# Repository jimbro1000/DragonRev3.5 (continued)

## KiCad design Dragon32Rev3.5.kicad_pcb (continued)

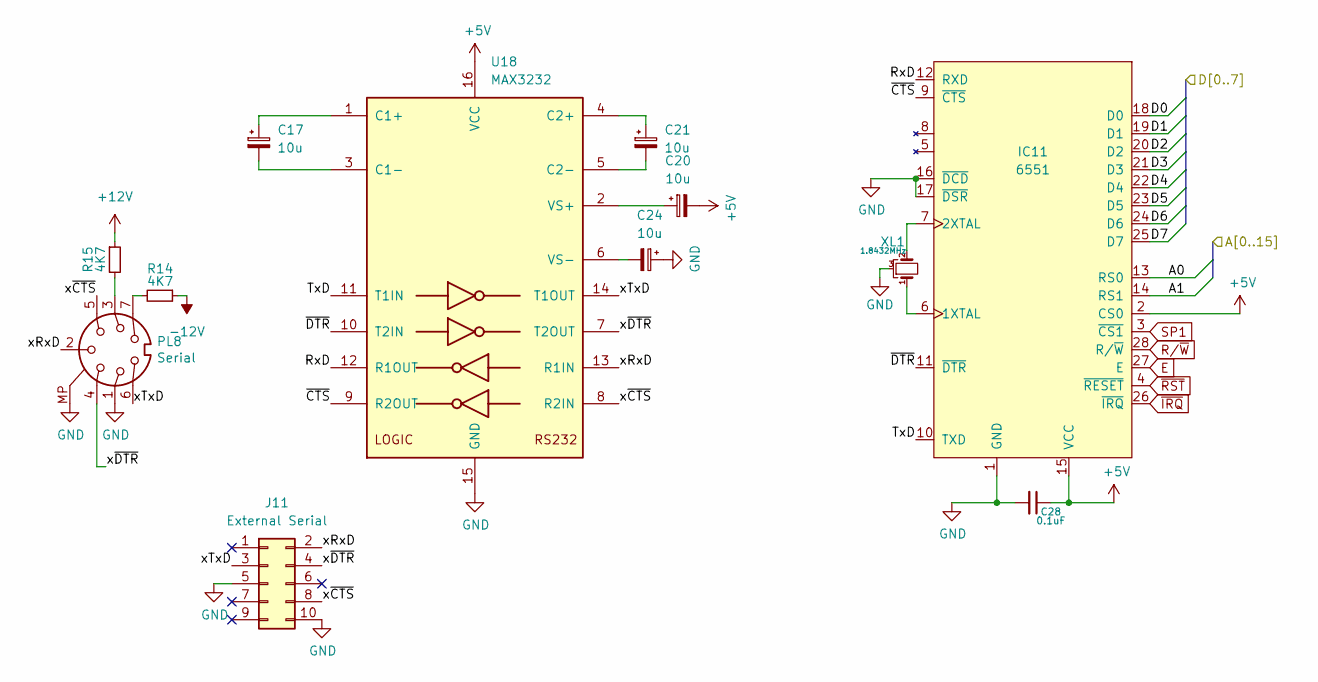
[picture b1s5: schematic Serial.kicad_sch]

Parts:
C17, C20, C21, C24: 10u; CP_EIA-3528-21_Kemet-B; DigiKey 478-5257-1-ND
C28: 0.1uF; C_0805_2012Metric
IC11: 6551; DIP-28_W15.24mm_Socket
J11: External Serial; IDC-Header_2x05_P2.54mm_Vertical
PL8: Serial; DIN-7_DELTRON_671-0701_Horizontal
R14, R15: 4K7; R_0402_1005Metric; DigiKey YAG1446CT-ND
U18: MAX3232; SOIC-16_3.9x9.9mm_P1.27mm; DigiKey 296-19851-1-ND
XL1: 1.8432MHz; Crystal_HC49-U_Horizontal_1EP_style2; DigiKey 2151-A-1.8432-18-ND

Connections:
+5V: C20.2, C28.1, IC11.2 (CS0), IC11.15 (VCC), U18.16 (VCC); also elsewhere on the board
+12V: R15.1; also elsewhere on the board
-12V: R14.1; also elsewhere on the board
/Audio/A0: IC11.13 (RS0); also elsewhere on the board
/Audio/A1: IC11.14 (RS1); also elsewhere on the board
/Audio/D0: IC11.18 (D0); also elsewhere on the board
/Audio/D1: IC11.19 (D1); also elsewhere on the board
/Audio/D2: IC11.20 (D2); also elsewhere on the board
/Audio/D3: IC11.21 (D3); also elsewhere on the board
/Audio/D4: IC11.22 (D4); also elsewhere on the board
/Audio/D5: IC11.23 (D5); also elsewhere on the board
/Audio/D6: IC11.24 (D6); also elsewhere on the board
/Audio/D7: IC11.25 (D7); also elsewhere on the board
/Serial/RxD: IC11.12 (RXD), U18.12 (R1OUT)
/Serial/TxD: IC11.10 (TXD), U18.11 (T1IN)
/Serial/xRxD: J11.2, PL8.2, U18.13 (R1IN)
/Serial/xTxD: J11.3, PL8.6, U18.14 (T1OUT)
/Serial/x~CTS: J11.8, PL8.5, U18.8 (R2IN)
/Serial/x~DTR: J11.4, PL8.4, U18.7 (T2OUT)
/Serial/~CTS: IC11.9 (~CTS), U18.9 (R2OUT)
/Serial/~DTR: IC11.11 (~DTR), U18.10 (T2IN)
E: IC11.27 (E); also elsewhere on the board
GND: C24.1, C28.2, IC11.1 (GND), IC11.16 (~DCD), IC11.17 (~DSR), J11.5, J11.10, PL8.1, PL8.MP, U18.15 (GND), XL1.3; also elsewhere on the board
unnamed: IC11.6 (1XTAL), XL1.1
unnamed: IC11.7 (2XTAL), XL1.2
unnamed: PL8.3, R15.2
unnamed: PL8.7, R14.2
unnamed: C17.1, U18.1 (C1+)
unnamed: C17.2, U18.3 (C1-)
unnamed: C21.1, U18.4 (C2+)
unnamed: C21.2, U18.5 (C2-)
unnamed: C20.1, U18.2 (VS+)
unnamed: C24.2, U18.6 (VS-)
R/~W: IC11.28 (R/~W); also elsewhere on the board
SP1: IC11.3 (~CS1); also elsewhere on the board
~IRQ: IC11.26 (~IRQ); also elsewhere on the board
~RST: IC11.4 (~RESET); also elsewhere on the board

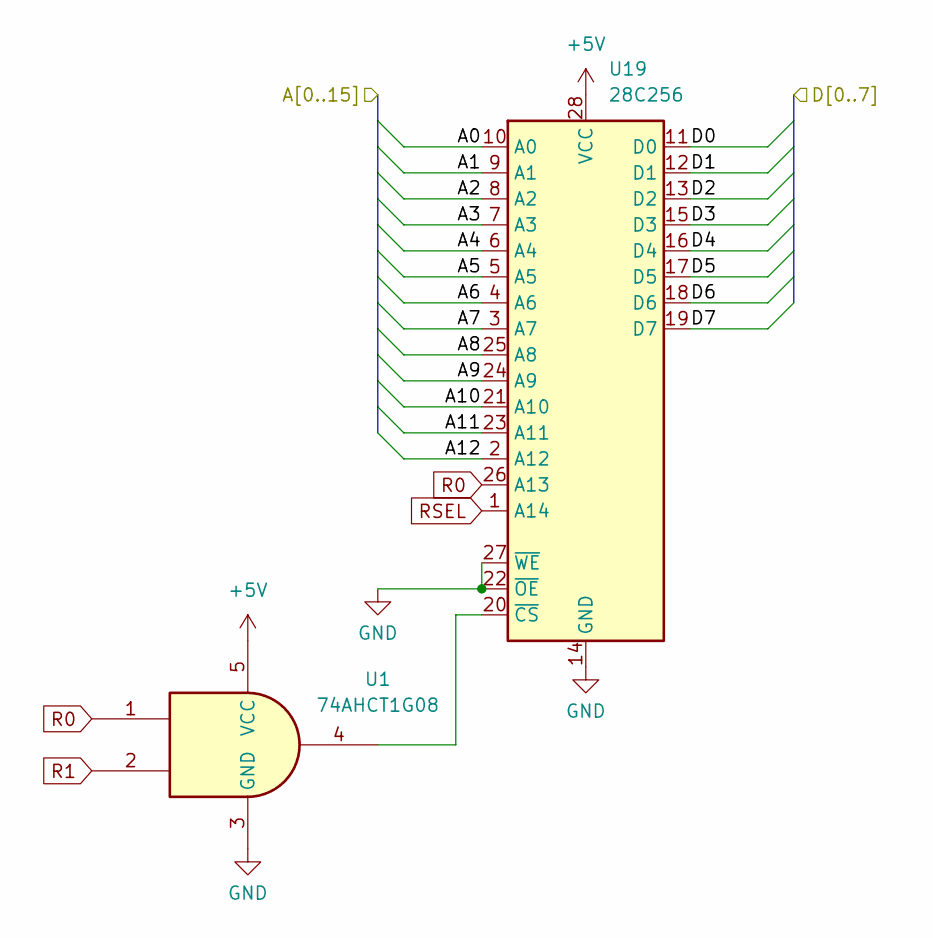
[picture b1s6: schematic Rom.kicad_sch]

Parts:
U1: 74AHCT1G08; SOT-353_SC-70-5
U19: 28C256; DIP-28_W15.24mm_Socket

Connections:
+5V: U1.5 (VCC), U19.25 (A8), U19.28 (VCC); also elsewhere on the board
/Audio/A0: U19.10 (A0); also elsewhere on the board
/Audio/A1: U19.9 (A1); also elsewhere on the board
/Audio/A2: U19.8 (A2); also elsewhere on the board
/Audio/A3: U19.7 (A3); also elsewhere on the board
/Audio/A4: U19.6 (A4); also elsewhere on the board
/Audio/A5: U19.5 (A5); also elsewhere on the board
/Audio/A6: U19.4 (A6); also elsewhere on the board
/Audio/A7: U19.3 (A7); also elsewhere on the board
/Audio/A9: U19.24 (A9); also elsewhere on the board
/Audio/A10: U19.21 (A10); also elsewhere on the board
/Audio/A11: U19.23 (A11); also elsewhere on the board
/Audio/A12: U19.2 (A12); also elsewhere on the board
/Audio/D0: U19.11 (D0); also elsewhere on the board
/Audio/D1: U19.12 (D1); also elsewhere on the board
/Audio/D2: U19.13 (D2); also elsewhere on the board
/Audio/D3: U19.15 (D3); also elsewhere on the board
/Audio/D4: U19.16 (D4); also elsewhere on the board
/Audio/D5: U19.17 (D5); also elsewhere on the board
/Audio/D6: U19.18 (D6); also elsewhere on the board
/Audio/D7: U19.19 (D7); also elsewhere on the board
GND: U1.3 (GND), U19.14 (GND), U19.22 (~OE), U19.27 (~WE); also elsewhere on the board
unnamed: U1.4, U19.20 (~CS)
R0: U1.1, U19.26 (A13); also elsewhere on the board
R1: U1.2; also elsewhere on the board
RSEL: U19.1 (A14); also elsewhere on the board

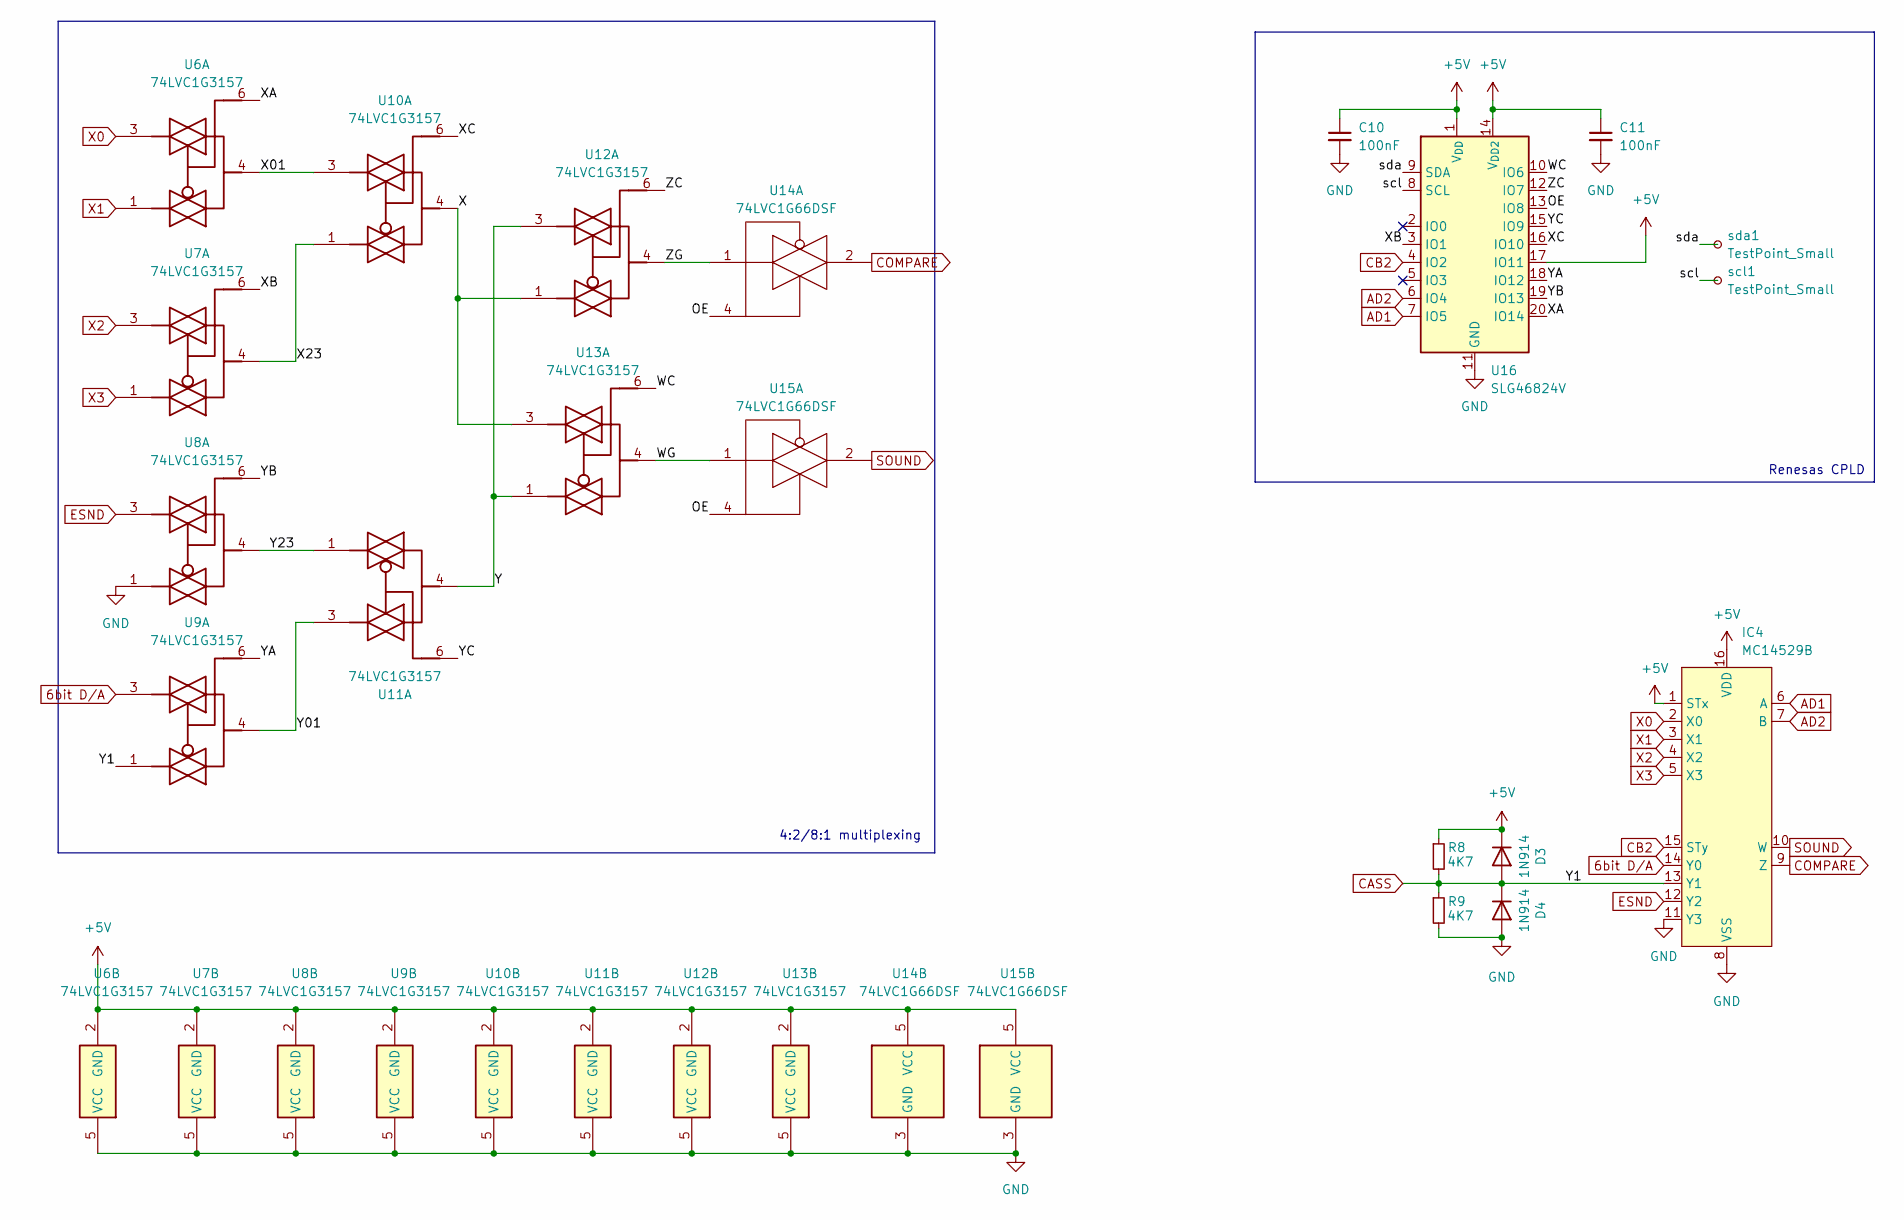
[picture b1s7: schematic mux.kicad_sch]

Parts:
C10, C11: 100nF; C_0402_1005Metric; DigiKey 1276-CL05B104KP5VPNCCT-ND
D3, D4: 1N914; D_SOD-523; DigiKey 1N914BWTCT-ND
IC4: MC14529B; DIP-16_W7.62mm; DigiKey CD4529BCN-ND
R8, R9: 4K7; R_0402_1005Metric; DigiKey YAG1446CT-ND
U6, U7, U8, U9, U10, U11, U12, U13: 74LVC1G3157; SOT-363_SC-70-6; DigiKey 1727-3491-1-ND
U14, U15: 74LVC1G66DSF; SOT-353_SC-70-5; LCSC C2673638
U16: SLG46824V; Renesas_UQFN-20_2x3mm_P0.4mm_LayoutBorder4x6y; DigiKey 1695-SLG46824VCT-ND
scl1: TestPoint_Small; TestPoint_Pad_D1.0mm
sda1: TestPoint_Small; TestPoint_Pad_D1.0mm

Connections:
6bit D/A: IC4.14 (Y0), U9.3; also elsewhere on the board
+5V: C10.1, C11.1, D3.1 (K), IC4.1 (STx), IC4.16 (VDD), R8.1, U6.2 (GND), U7.2 (GND), U8.2 (GND), U9.2 (GND), U10.2 (GND), U11.2 (GND), U12.2 (GND), U13.2 (GND), U14.5 (VCC), U15.5 (VCC), U16.1 (V_{DD}), U16.14 (V_{DD2}), U16.17 (IO11); also elsewhere on the board
/Devices/MC14529/OE: U14.4, U15.4, U16.13 (IO8)
/Devices/MC14529/WC: U13.6, U16.10 (IO6)
/Devices/MC14529/WG: U13.4, U15.1
/Devices/MC14529/X: U10.4, U12.1, U13.3
/Devices/MC14529/X01: U6.4, U10.3
/Devices/MC14529/X23: U7.4, U10.1
/Devices/MC14529/XA: U6.6, U16.20 (IO14)
/Devices/MC14529/XB: U7.6, U16.3 (IO1)
/Devices/MC14529/XC: U10.6, U16.16 (IO10)
/Devices/MC14529/Y: U11.4, U12.3, U13.1
/Devices/MC14529/Y01: U9.4, U11.3
/Devices/MC14529/Y23: U8.4, U11.1
/Devices/MC14529/YA: U9.6, U16.18 (IO12)
/Devices/MC14529/YB: U8.6, U16.19 (IO13)
/Devices/MC14529/YC: U11.6, U16.15 (IO9)
/Devices/MC14529/ZC: U12.6, U16.12 (IO7)
/Devices/MC14529/ZG: U12.4, U14.1
/Devices/MC14529/scl: U16.8 (SCL), scl1.1
/Devices/MC14529/sda: U16.9 (SDA), sda1.1
AD1: IC4.6 (A), U16.7 (IO5); also elsewhere on the board
AD2: IC4.7 (B), U16.6 (IO4); also elsewhere on the board
CASS: D3.2 (A), D4.1 (K), IC4.13 (Y1), R8.2, R9.1, U9.1; also elsewhere on the board
CB2: IC4.15 (STy), U16.4 (IO2); also elsewhere on the board
COMPARE: IC4.9 (Z), U14.2; also elsewhere on the board
ESND: IC4.12 (Y2), U8.3; also elsewhere on the board
GND: C10.2, C11.2, D4.2 (A), IC4.8 (VSS), IC4.11 (Y3), R9.2, U6.5 (VCC), U7.5 (VCC), U8.1, U8.5 (VCC), U9.5 (VCC), U10.5 (VCC), U11.5 (VCC), U12.5 (VCC), U13.5 (VCC), U14.3 (GND), U15.3 (GND), U16.11 (GND); also elsewhere on the board
SOUND: IC4.10 (W), U15.2; also elsewhere on the board
X0: IC4.2 (X0), U6.3; also elsewhere on the board
X1: IC4.3 (X1), U6.1; also elsewhere on the board
X2: IC4.4 (X2), U7.3; also elsewhere on the board
X3: IC4.5 (X3), U7.1; also elsewhere on the board

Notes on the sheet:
4:2/8:1 multiplexing
Renesas CPLD

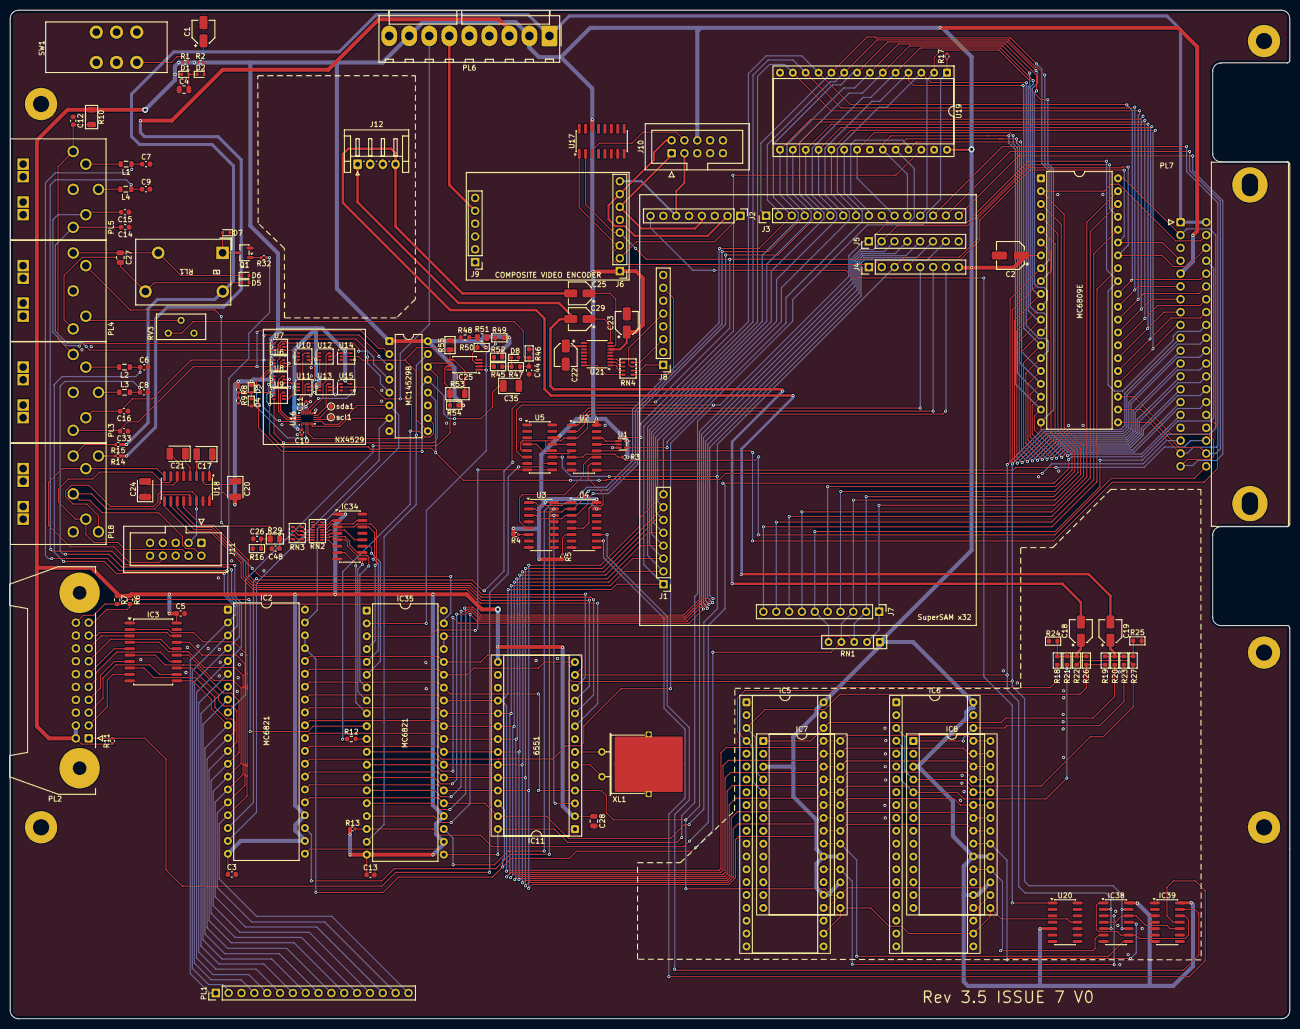
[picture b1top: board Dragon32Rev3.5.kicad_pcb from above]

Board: 2 copper layers, 253.0 x 199.4 mm, 156 parts (0 on the bottom side), 222 nets.

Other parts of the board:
M1, M3, M4, M7, M8: MountingHole_3.2mm_M3_Pad

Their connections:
GND: M1.1, M3.1, M4.1, M7.1, M8.1; also elsewhere on the board

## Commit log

2026-06-04 update readme with design notes
2026-06-11 add audio support
